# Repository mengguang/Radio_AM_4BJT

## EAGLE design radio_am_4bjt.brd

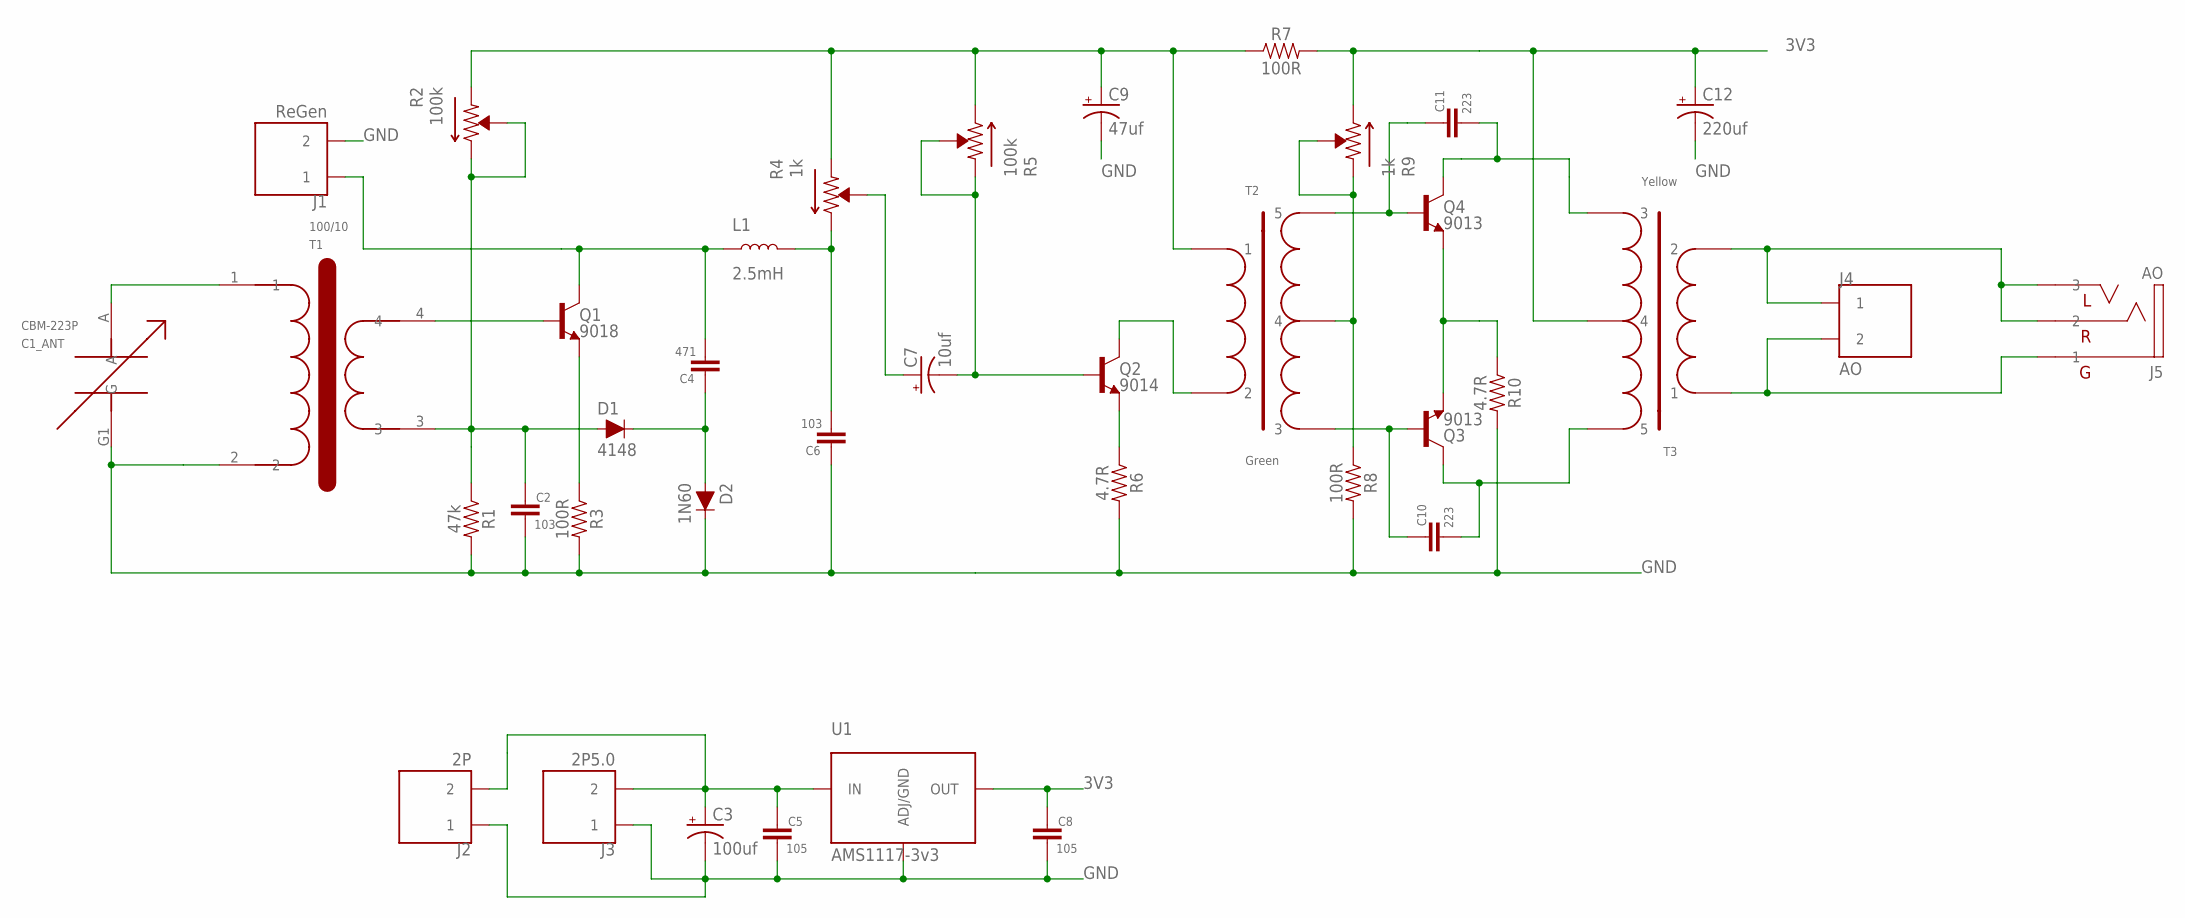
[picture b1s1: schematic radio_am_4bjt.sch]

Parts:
C1: CBM-223P
C2, C6: 103; CAP_5MM
C3: 100uf; CAP_2.5MM
C4: 471; CAP_5MM
C5, C8: 105; CAP_5MM
C7: 10uf; CAP_2MM
C9: 47uf; CAP_2MM
C10, C11: 223; CAP_5MM
C12: 220uf; CAP_2.5MM
D1: 4148; DIODE-1N4148
D2: 1N60; DIODE-1N4148
J1: ReGen; 2P_2.54MM
J2: 2P; 2P_2.54MM
J3: 2P5.0; 2P_5.08MM
J4: AO; 2P_5.08MM
J5: AO; 3.5MM
L1: 2.5mH; VLU0810
Q1: 9018; TO-92
Q2: 9014; TO-92
Q3, Q4: 9013; TO-92
R1: 47k; AXIAL-0.3
R2, R5: 100k; 3362P
R3, R7, R8: 100R; AXIAL-0.3
R4, R9: 1k; 3362P
R6, R10: 4.7R; AXIAL-0.3
T1: 100/10; AM_ANT_COIL
T2: Green; TRANSFORMER_BJT_PP_2_4
T3: Yellow; TRANSFORMER_BJT_PP_2_4
U1: AMS1117-3v3; SOT-223

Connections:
3V3: C8.P$1 (1), C12.+, R7.P$2 (2), R9.P$3 (3), T3.4, U1.2 (OUT), U1.4 (OUT)
GND: C1.G1 (G), C2.P$2 (2), C3.-, C5.P$2 (2), C6.P$1 (1), C8.P$2 (2), C9.-, C12.-, D2.C, J1.2, J2.1, J3.L (1), R1.P$2 (2), R3.P$2 (2), R6.P$2 (2), R8.P$2 (2), R10.P$2 (2), T1.2, U1.1 (ADJ/GND)
unnamed: C1.A, T1.1
unnamed: Q1.2 (B), T1.4
unnamed: Q2.1 (E), R6.P$1 (1)
unnamed: C4.P$1 (1), D1.C, D2.A
unnamed: C4.P$2 (2), J1.1, L1.+ (1), Q1.3 (C)
unnamed: C7.+, R4.P$2 (2)
unnamed: C9.+, R2.P$1 (1), R4.P$1 (1), R5.P$3 (3), R7.P$1 (1), T2.1
unnamed: C6.P$2 (2), L1.- (2), R4.P$3 (3)
unnamed: C7.-, Q2.2 (B), R5.P$1 (1), R5.P$2 (2)
unnamed: C11.P$2 (2), Q4.3 (C), T3.3
unnamed: C10.P$2 (2), Q3.3 (C), T3.5
unnamed: R8.P$1 (1), R9.P$1 (1), R9.P$2 (2), T2.4
unnamed: C10.P$1 (1), Q3.2 (B), T2.3
unnamed: C11.P$1 (1), Q4.2 (B), T2.5
unnamed: J4.N (2), J5.P$1 (1), T3.1
unnamed: J4.L (1), J5.P$2 (2), J5.P$3 (3), T3.2
unnamed: C2.P$1 (1), D1.A, R1.P$1 (1), R2.P$2 (2), R2.P$3 (3), T1.3
unnamed: C3.+, C5.P$1 (1), J2.2, J3.N (2), U1.3 (IN)
unnamed: Q3.1 (E), Q4.1 (E), R10.P$1 (1)
unnamed: Q1.1 (E), R3.P$1 (1)
unnamed: Q2.3 (C), T2.2

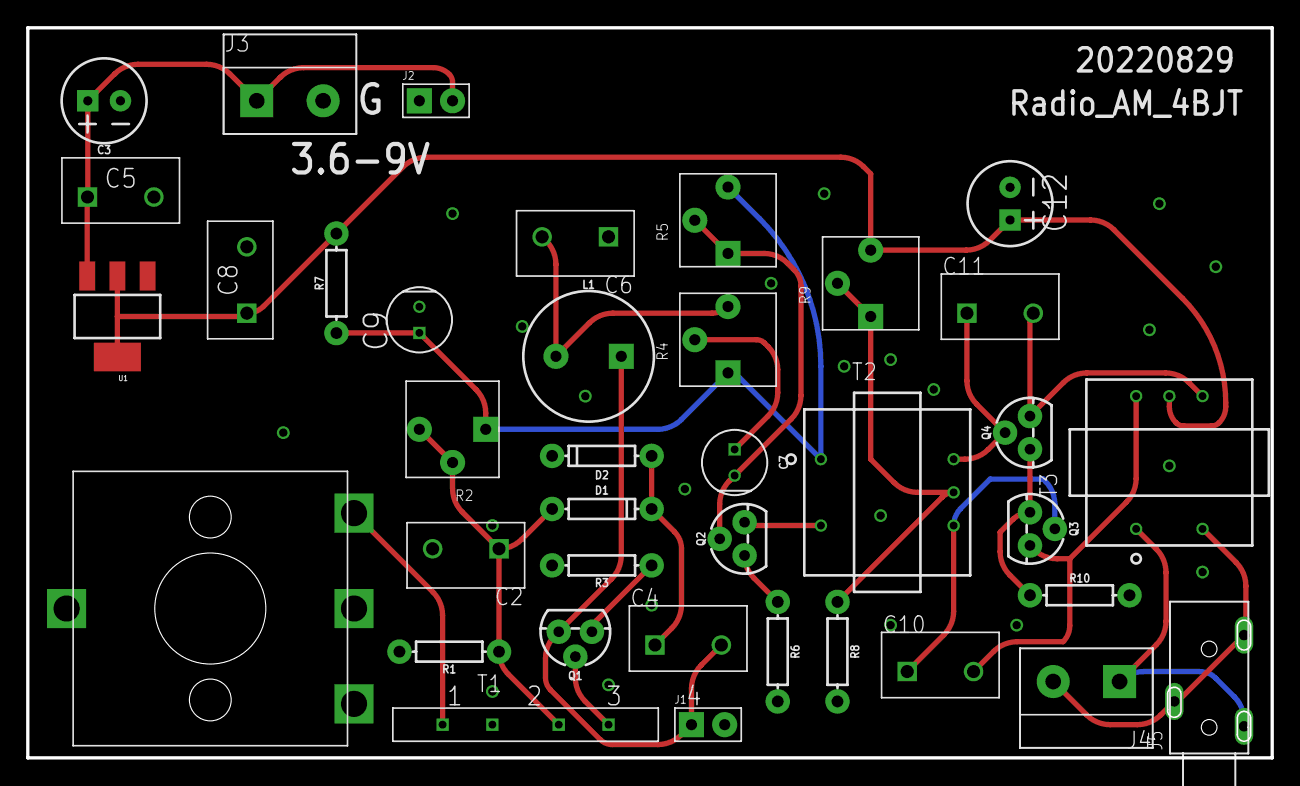
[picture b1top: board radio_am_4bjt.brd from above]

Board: 2 copper layers, 95.2 x 55.9 mm, 38 parts (0 on the bottom side), 23 nets.

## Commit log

2022-09-03 20220829
